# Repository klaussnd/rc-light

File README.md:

# Repository moved

This repository has moved to Europe: [https://codeberg.org/klaussnd/rc-light](https://codeberg.org/klaussnd/rc-light)

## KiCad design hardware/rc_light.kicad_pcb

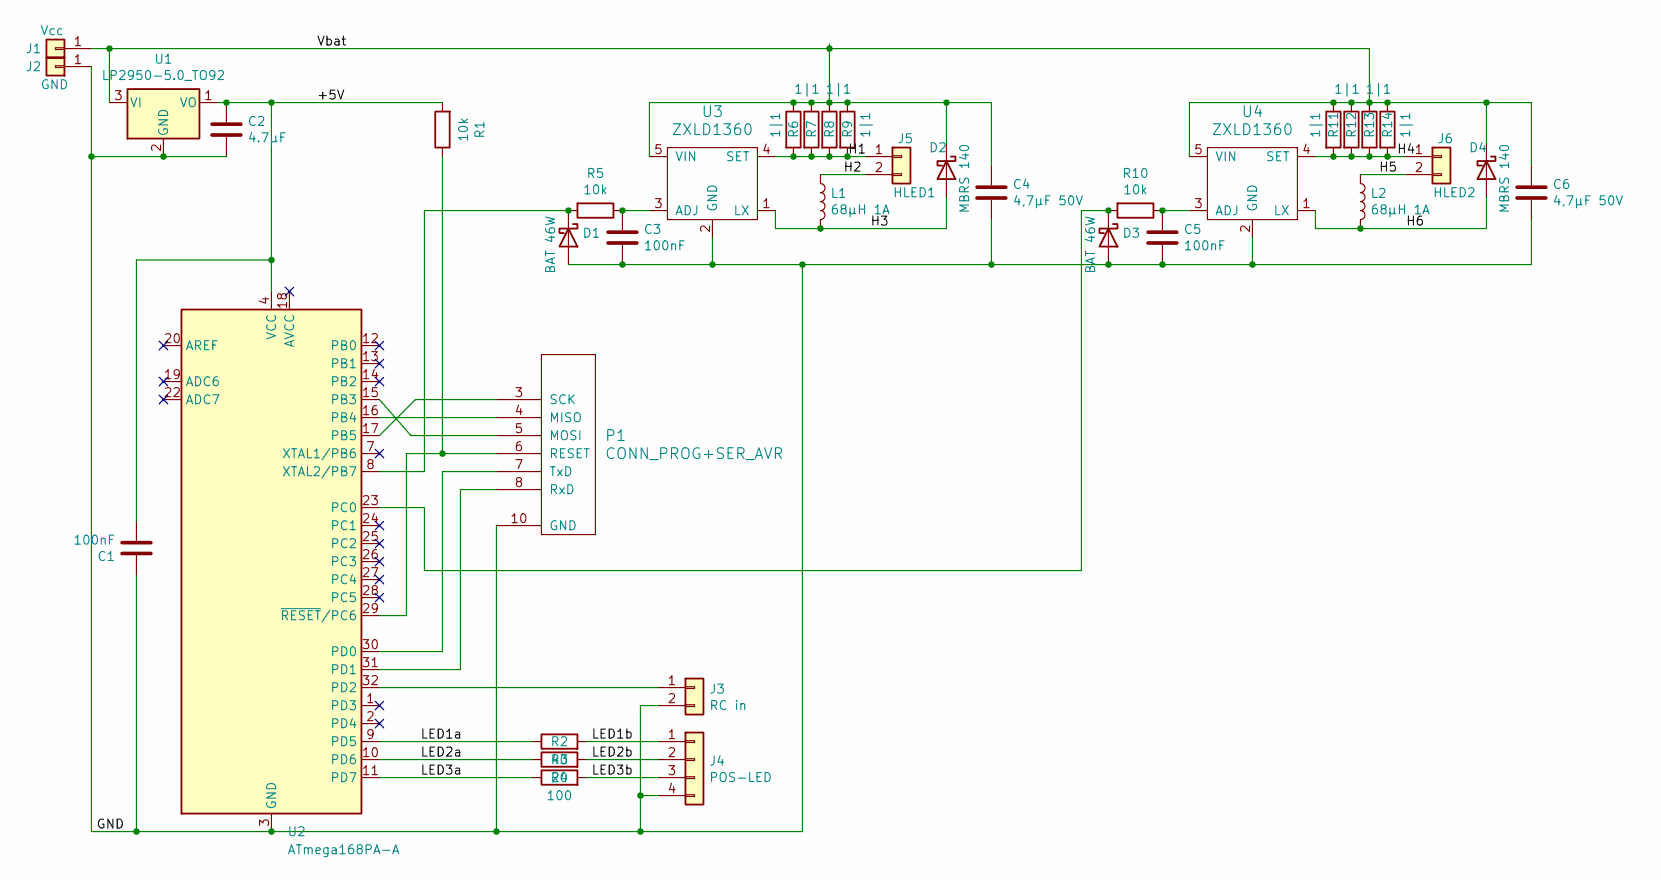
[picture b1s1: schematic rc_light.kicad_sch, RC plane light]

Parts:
C1, C3, C5: 100nF; C_0805_2012Metric
C2: 4.7µF; C_0805_2012Metric
C4, C6: 4,7µF 50V; C_1206_3216Metric
D1, D3: BAT 46W; D_SOD-123
D2, D4: MBRS 140; 403A
J1: Vcc; PIN_SMD
J2: GND; PIN_SMD
J3: RC in; PinSocket_1x02_P2.54mm_Vertical
J4: POS-LED; PinSocket_1x04_P2.54mm_Vertical
J5: HLED1; PinSocket_1x02_P2.54mm_Vertical
J6: HLED2; PinSocket_1x02_P2.54mm_Vertical
L1, L2: 68µH 1A; L-PISG
P1: CONN_PROG+SER_AVR; SIL-10_MYAVR+SER
R1, R5, R10: 10k; R_0805_2012Metric
R2: 40; R_0805_2012Metric
R3: 20; R_0805_2012Metric
R4: 100; R_0805_2012Metric
R6, R7, R8, R9, R11, R12, R13, R14: 1|1; R_0805_2012Metric
U1: LP2950-5.0_TO92; TO-92_HandSolder
U2: ATmega168PA-A; TQFP-32_7x7mm_P0.8mm
U3, U4: ZXLD1360; TSOT-23-5_HandSoldering

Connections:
/+5V: C1.2, C2.1, R1.2, U1.1 (VO), U2.4 (VCC), U2.6 (VCC)
/GND: C1.1, C2.2, C3.2, C4.2, C5.2, C6.2, D1.2 (A), D3.2 (A), J2.1, J3.2, J4.4, P1.10 (GND), U1.2 (GND), U2.3 (GND), U2.5 (GND), U2.21 (GND), U3.2 (GND), U4.2 (GND)
/H1: J5.1, R6.2, R7.2, R8.2, R9.2, U3.4 (SET)
/H2: J5.2, L1.1
/H3: D2.2 (A), L1.2, U3.1 (LX)
/H4: J6.1, R11.2, R12.2, R13.2, R14.2, U4.4 (SET)
/H5: J6.2, L2.1
/H6: D4.2 (A), L2.2, U4.1 (LX)
/LED1a: R2.1, U2.9 (PD5)
/LED1b: J4.1, R2.2
/LED2a: R3.1, U2.10 (PD6)
/LED2b: J4.2, R3.2
/LED3a: R4.1, U2.11 (PD7)
/LED3b: J4.3, R4.2
/Vbat: C4.1, C6.1, D2.1 (K), D4.1 (K), J1.1, R6.1, R7.1, R8.1, R9.1, R11.1, R12.1, R13.1, R14.1, U1.3 (VI), U3.5 (VIN), U4.5 (VIN)
unnamed: C3.1, R5.1, U3.3 (ADJ)
unnamed: C5.1, R10.1, U4.3 (ADJ)
unnamed: D1.1 (K), R5.2, U2.8 (XTAL2/PB7)
unnamed: D3.1 (K), R10.2, U2.23 (PC0)
unnamed: J3.1, U2.32 (PD2)
unnamed: P1.3 (SCK), U2.17 (PB5)
unnamed: P1.4 (MISO), U2.16 (PB4)
unnamed: P1.5 (MOSI), U2.15 (PB3)
unnamed: P1.6 (RESET), R1.1, U2.29 (~RESET/PC6)
unnamed: P1.7 (TxD), U2.30 (PD0)
unnamed: P1.8 (RxD), U2.31 (PD1)

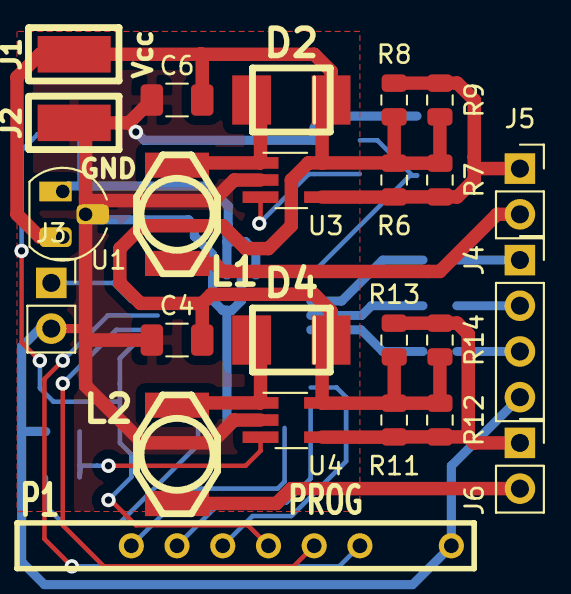
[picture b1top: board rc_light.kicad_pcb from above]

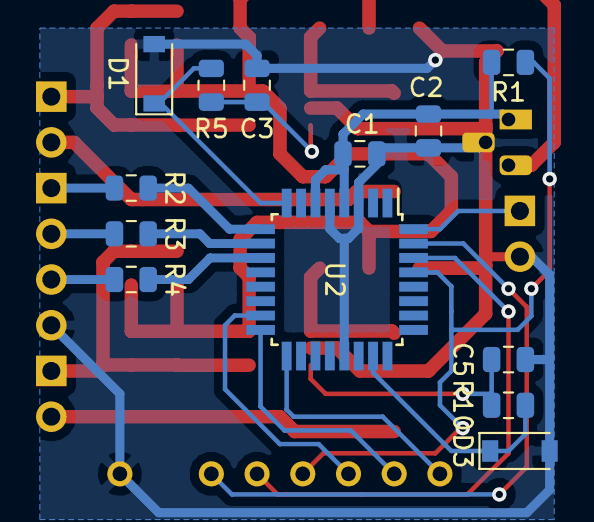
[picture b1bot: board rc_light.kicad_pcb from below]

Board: 2 copper layers, 37 parts (13 on the bottom side), 26 nets.

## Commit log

2024-05-26 Add board
2024-05-26 Add firmware
2024-05-26 Add documentation
2024-10-16 Improve README
2025-08-05 Add move notice
